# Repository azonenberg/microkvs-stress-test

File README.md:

# microkvs-stress-test
Stress test platform for microkvs in the presence of unexpected resets and power cycles

The basic concept is simple: two STM32L431s, with the first (test controller) able to reset or power cycle the second
(DUT).

The DUT

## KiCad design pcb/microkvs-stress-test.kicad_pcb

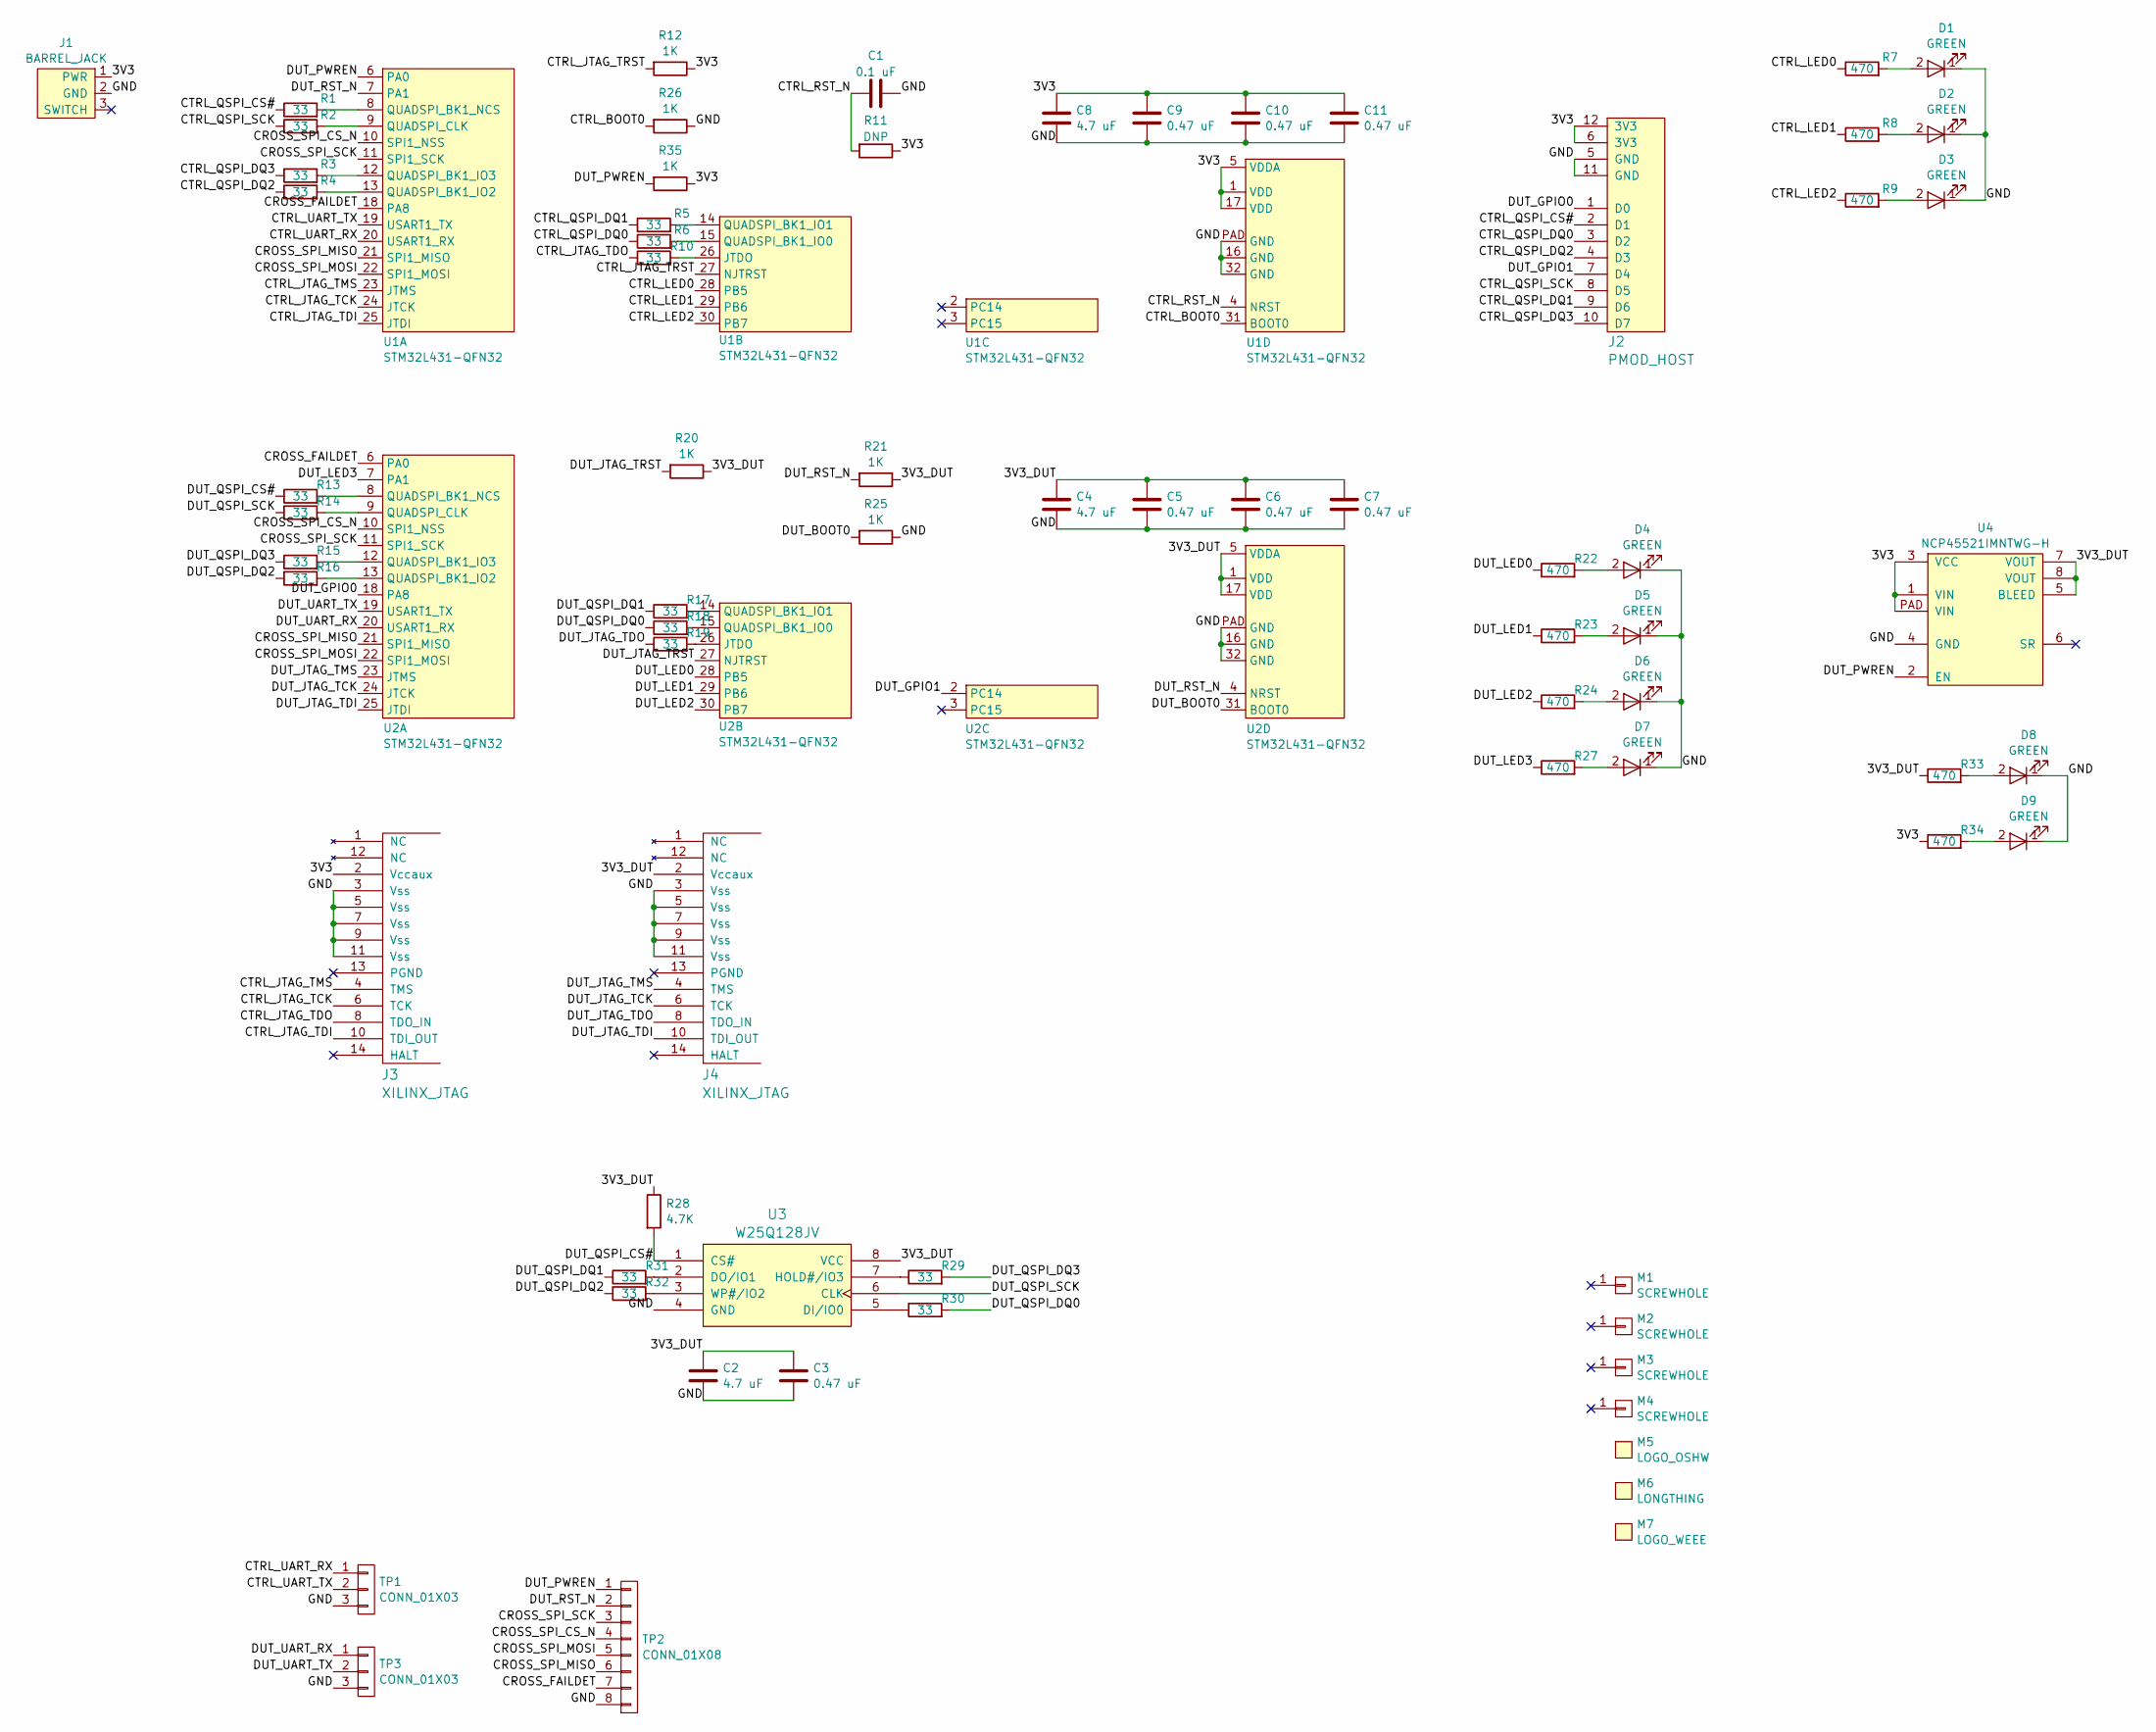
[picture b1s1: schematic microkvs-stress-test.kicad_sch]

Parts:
C1: 0.1 uF; EIA_0402_CAP_NOSILK
C2, C4, C8: 4.7 uF; EIA_0603_CAP_NOSILK
C3, C5, C6, C7, C9, C10, C11: 0.47 uF; EIA_0402_CAP_NOSILK
D1, D2, D3, D4, D5, D6, D7, D8, D9: GREEN; EIA_0603_LED
J1: BARREL_JACK; CONN_CUI_PJ-058BH_HIPWR_BARREL_NOSLOT
J2: PMOD_HOST; CONN_HEADER_2.54MM_2x6_RA_PMOD_HOST
J3, J4: XILINX_JTAG; XILINX_JTAG_PTH_MOLEX_0878311420
M1, M2, M3, M4: SCREWHOLE; MECHANICAL_CLEARANCEHOLE_4_40
M5: LOGO_OSHW; Logo_silk_OSHW_6x6mm
M6: LONGTHING; LONGTHING-1200DPI
M7: LOGO_WEEE; Logo_silk_WEEE_3.4x5mm
R1, R2, R3, R4, R5, R6, R10, R13, R14, R15, R16, R17, R18, R19, R29, R30, R31, R32: 33; EIA_0402_RES_NOSILK
R7, R8, R9, R22, R23, R24, R27, R33, R34: 470; EIA_0402_RES_NOSILK
R11: DNP; EIA_0402_RES_NOSILK
R12, R20, R21, R25, R26, R35: 1K; EIA_0402_RES_NOSILK
R28: 4.7K; EIA_0402_RES_NOSILK
TP1, TP3: CONN_01X03; CONN_HEADER_2.54MM_1x3
TP2: CONN_01X08; CONN_HEADER_2.54MM_1x8
U1, U2: STM32L431-QFN32; QFN_32_0.5MM_5x5MM
U3: W25Q128JV; DFN_8_1.27MM_6x5MM
U4: NCP45521IMNTWG-H; DFN_8_0.5MM_2x2MM

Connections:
/3V3: C8.1, C9.1, C10.1, C11.1, J1.1 (PWR), J2.6 (3V3), J2.12 (3V3), J3.2 (Vccaux), R11.1, R12.1, R34.1, R35.1, U1.1 (VDD), U1.5 (VDDA), U1.17 (VDD), U4.1 (VIN), U4.3 (VCC), U4.PAD (VIN)
/3V3_DUT: C2.1, C3.1, C4.1, C5.1, C6.1, C7.1, J4.2 (Vccaux), R20.1, R21.1, R28.1, R33.1, U2.1 (VDD), U2.5 (VDDA), U2.17 (VDD), U3.8 (VCC), U4.5 (BLEED), U4.7 (VOUT), U4.8 (VOUT)
/CROSS_FAILDET: TP2.7, U1.18 (PA8), U2.6 (PA0)
/CROSS_SPI_CS_N: TP2.4, U1.10 (SPI1_NSS), U2.10 (SPI1_NSS)
/CROSS_SPI_MISO: TP2.6, U1.21 (SPI1_MISO), U2.21 (SPI1_MISO)
/CROSS_SPI_MOSI: TP2.5, U1.22 (SPI1_MOSI), U2.22 (SPI1_MOSI)
/CROSS_SPI_SCK: TP2.3, U1.11 (SPI1_SCK), U2.11 (SPI1_SCK)
/CTRL_BOOT0: R26.2, U1.31 (BOOT0)
/CTRL_JTAG_TCK: J3.6 (TCK), U1.24 (JTCK)
/CTRL_JTAG_TDI: J3.10 (TDI_OUT), U1.25 (JTDI)
/CTRL_JTAG_TDO: J3.8 (TDO_IN), R10.1
/CTRL_JTAG_TMS: J3.4 (TMS), U1.23 (JTMS)
/CTRL_JTAG_TRST: R12.2, U1.27 (NJTRST)
/CTRL_LED0: R7.1, U1.28 (PB5)
/CTRL_LED1: R8.1, U1.29 (PB6)
/CTRL_LED2: R9.1, U1.30 (PB7)
/CTRL_QSPI_CS#: J2.2 (D1), R1.1
/CTRL_QSPI_DQ0: J2.3 (D2), R6.1
/CTRL_QSPI_DQ1: J2.9 (D6), R5.1
/CTRL_QSPI_DQ2: J2.4 (D3), R4.1
/CTRL_QSPI_DQ3: J2.10 (D7), R3.1
/CTRL_QSPI_SCK: J2.8 (D5), R2.1
/CTRL_RST_N: C1.1, R11.2, U1.4 (NRST)
/CTRL_UART_RX: TP1.1, U1.20 (USART1_RX)
/CTRL_UART_TX: TP1.2, U1.19 (USART1_TX)
/DUT_BOOT0: R25.2, U2.31 (BOOT0)
/DUT_GPIO0: J2.1 (D0), U2.18 (PA8)
/DUT_GPIO1: J2.7 (D4), U2.2 (PC14)
/DUT_JTAG_TCK: J4.6 (TCK), U2.24 (JTCK)
/DUT_JTAG_TDI: J4.10 (TDI_OUT), U2.25 (JTDI)
/DUT_JTAG_TDO: J4.8 (TDO_IN), R19.1
/DUT_JTAG_TMS: J4.4 (TMS), U2.23 (JTMS)
/DUT_JTAG_TRST: R20.2, U2.27 (NJTRST)
/DUT_LED0: R22.1, U2.28 (PB5)
/DUT_LED1: R23.1, U2.29 (PB6)
/DUT_LED2: R24.1, U2.30 (PB7)
/DUT_LED3: R27.1, U2.7 (PA1)
/DUT_PWREN: R35.2, TP2.1, U1.6 (PA0), U4.2 (EN)
/DUT_QSPI_CS#: R13.1, R28.2, U3.1 (CS#)
/DUT_QSPI_DQ0: R18.1, R30.2
/DUT_QSPI_DQ1: R17.1, R31.1
/DUT_QSPI_DQ2: R16.1, R32.1
/DUT_QSPI_DQ3: R15.1, R29.2
/DUT_QSPI_SCK: R14.1, U3.6 (CLK)
/DUT_RST_N: R21.2, TP2.2, U1.7 (PA1), U2.4 (NRST)
/DUT_UART_RX: TP3.1, U2.20 (USART1_RX)
/DUT_UART_TX: TP3.2, U2.19 (USART1_TX)
/GND: C1.2, C2.2, C3.2, C4.2, C5.2, C6.2, C7.2, C8.2, C9.2, C10.2, C11.2, D1.1 (K), D2.1 (K), D3.1 (K), D4.1 (K), D5.1 (K), D6.1 (K), D7.1 (K), D8.1 (K), D9.1 (K), J1.2 (GND), J2.5 (GND), J2.11 (GND), J3.3 (Vss), J3.5 (Vss), J3.7 (Vss), J3.9 (Vss), J3.11 (Vss), J4.3 (Vss), J4.5 (Vss), J4.7 (Vss), J4.9 (Vss), J4.11 (Vss), R25.1, R26.1, TP1.3, TP2.8, TP3.3, U1.16 (GND), U1.32 (GND), U1.PAD (GND), U2.16 (GND), U2.32 (GND), U2.PAD (GND), U3.4 (GND), U4.4 (GND)
unnamed: D1.2 (A), R7.2
unnamed: D2.2 (A), R8.2
unnamed: D3.2 (A), R9.2
unnamed: D4.2 (A), R22.2
unnamed: D5.2 (A), R23.2
unnamed: D6.2 (A), R24.2
unnamed: D7.2 (A), R27.2
unnamed: D8.2 (A), R33.2
unnamed: D9.2 (A), R34.2
unnamed: R1.2, U1.8 (QUADSPI_BK1_NCS)
unnamed: R2.2, U1.9 (QUADSPI_CLK)
unnamed: R3.2, U1.12 (QUADSPI_BK1_IO3)
unnamed: R4.2, U1.13 (QUADSPI_BK1_IO2)
unnamed: R5.2, U1.14 (QUADSPI_BK1_IO1)
unnamed: R6.2, U1.15 (QUADSPI_BK1_IO0)
unnamed: R10.2, U1.26 (JTDO)
unnamed: R13.2, U2.8 (QUADSPI_BK1_NCS)
unnamed: R14.2, U2.9 (QUADSPI_CLK)
unnamed: R15.2, U2.12 (QUADSPI_BK1_IO3)
unnamed: R16.2, U2.13 (QUADSPI_BK1_IO2)
unnamed: R17.2, U2.14 (QUADSPI_BK1_IO1)
unnamed: R18.2, U2.15 (QUADSPI_BK1_IO0)
unnamed: R19.2, U2.26 (JTDO)
unnamed: R30.1, U3.5 (DI/IO0)
unnamed: R31.2, U3.2 (DO/IO1)
unnamed: R29.1, U3.7 (HOLD#/IO3)
unnamed: R32.2, U3.3 (WP#/IO2)

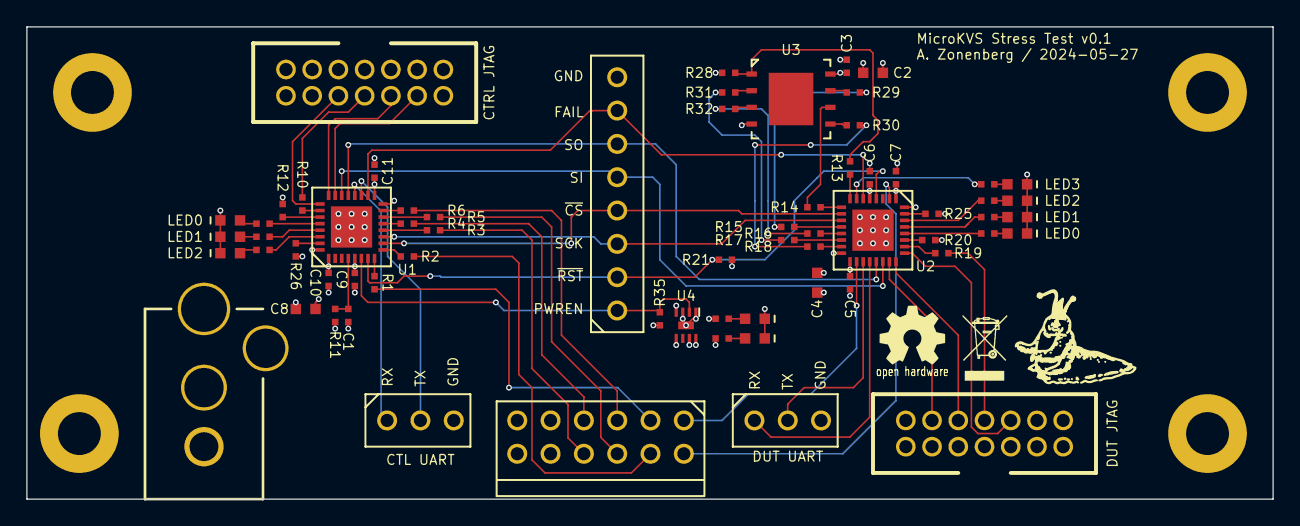
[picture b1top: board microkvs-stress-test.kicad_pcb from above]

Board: 4 copper layers, 95.0 x 36.0 mm, 73 parts (0 on the bottom side), 75 nets.

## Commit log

2024-05-27 Initial version of schematic
2024-05-27 Finished initial microkvs-stress-test board design
2024-05-27 Updated silkscreen with markings for controller LEDs
2024-06-11 Initial submodule import
2024-06-11 Initial bringup dongle config
2024-06-11 Initial skeleton firmware for control processor. Just brings up UART and turns on all LEDs
2024-06-11 Initial version of DUT MCU firmware
2024-06-12 Initial DUT firmware with basic KVS test
2024-06-19 Updated DUT to do less printing so it spends more time actually hammering on flash and less waiting on the UART. Also assert PA0 on failure
2024-06-21 Added initial NMI handling, more work on fuzzing in general
2024-06-21 Updated submodules
2024-06-22 Updated microkvs
2024-06-23 Sanity check that header values are within range
